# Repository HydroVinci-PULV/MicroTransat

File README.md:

# Architecture
Ceci est une ébauche de l'architecture finale des systèmes embarqués du bateau.

Cette présentation de l'architecture est amenée à évoluer en fonction des besoins du projet.

> **Note :** Les protocoles de communications entre les différents composants ne sont pas représentatifs de la réalité puisque le choix des composants n'est pas définitif à ce stade.

# Composants

## Ordinateur de bord

<p>Considérant que notre bateau autonomme puisse être apparenté à un drone, nous avons fait le choix d'utiliser un <i>flight controller</i> comme ordinateur de bord. C'est pourquoi nous utilisons au sein de notre architecture de navigation un <i>BeagleBone Blue</i> choisit pour sa compatibilité avec .</p>

Vous trouverez plus d'information sur le *BeagleBone Blue* sur [la page dédiée](../../wiki/BeagleBone-Blue) dans le wiki du projet.

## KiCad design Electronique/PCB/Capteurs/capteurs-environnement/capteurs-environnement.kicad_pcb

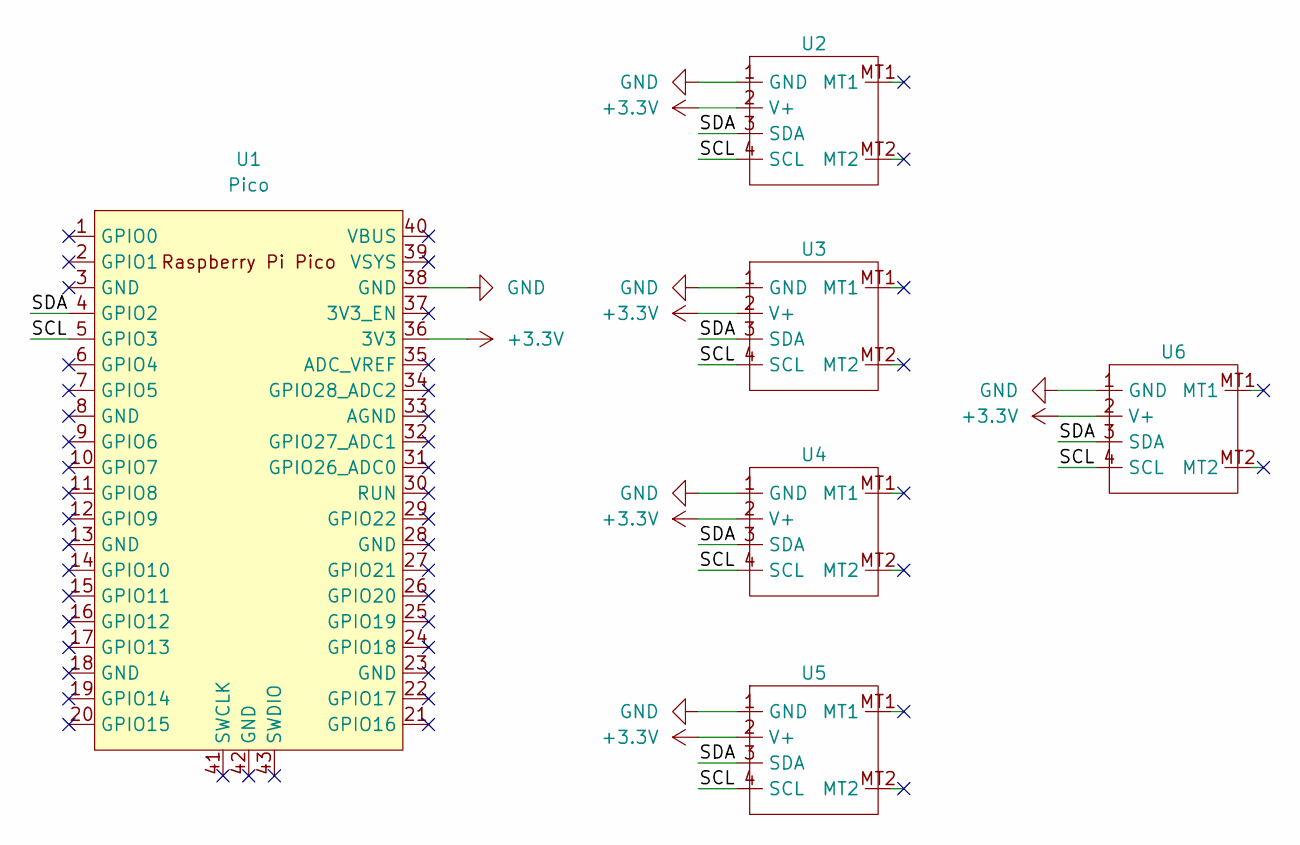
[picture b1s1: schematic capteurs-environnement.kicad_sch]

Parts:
U1: Pico; RPi_Pico_SMD_TH
U2, U3, U4, U5, U6: JST_SH4

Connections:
+3.3V: U1.36 (3V3), U2.2 (V+), U3.2 (V+), U4.2 (V+), U5.2 (V+), U6.2 (V+)
/SCL: U1.5 (GPIO3), U2.4 (SCL), U3.4 (SCL), U4.4 (SCL), U5.4 (SCL), U6.4 (SCL)
/SDA: U1.4 (GPIO2), U2.3 (SDA), U3.3 (SDA), U4.3 (SDA), U5.3 (SDA), U6.3 (SDA)
GND: U1.38 (GND), U2.1 (GND), U3.1 (GND), U4.1 (GND), U5.1 (GND), U6.1 (GND)

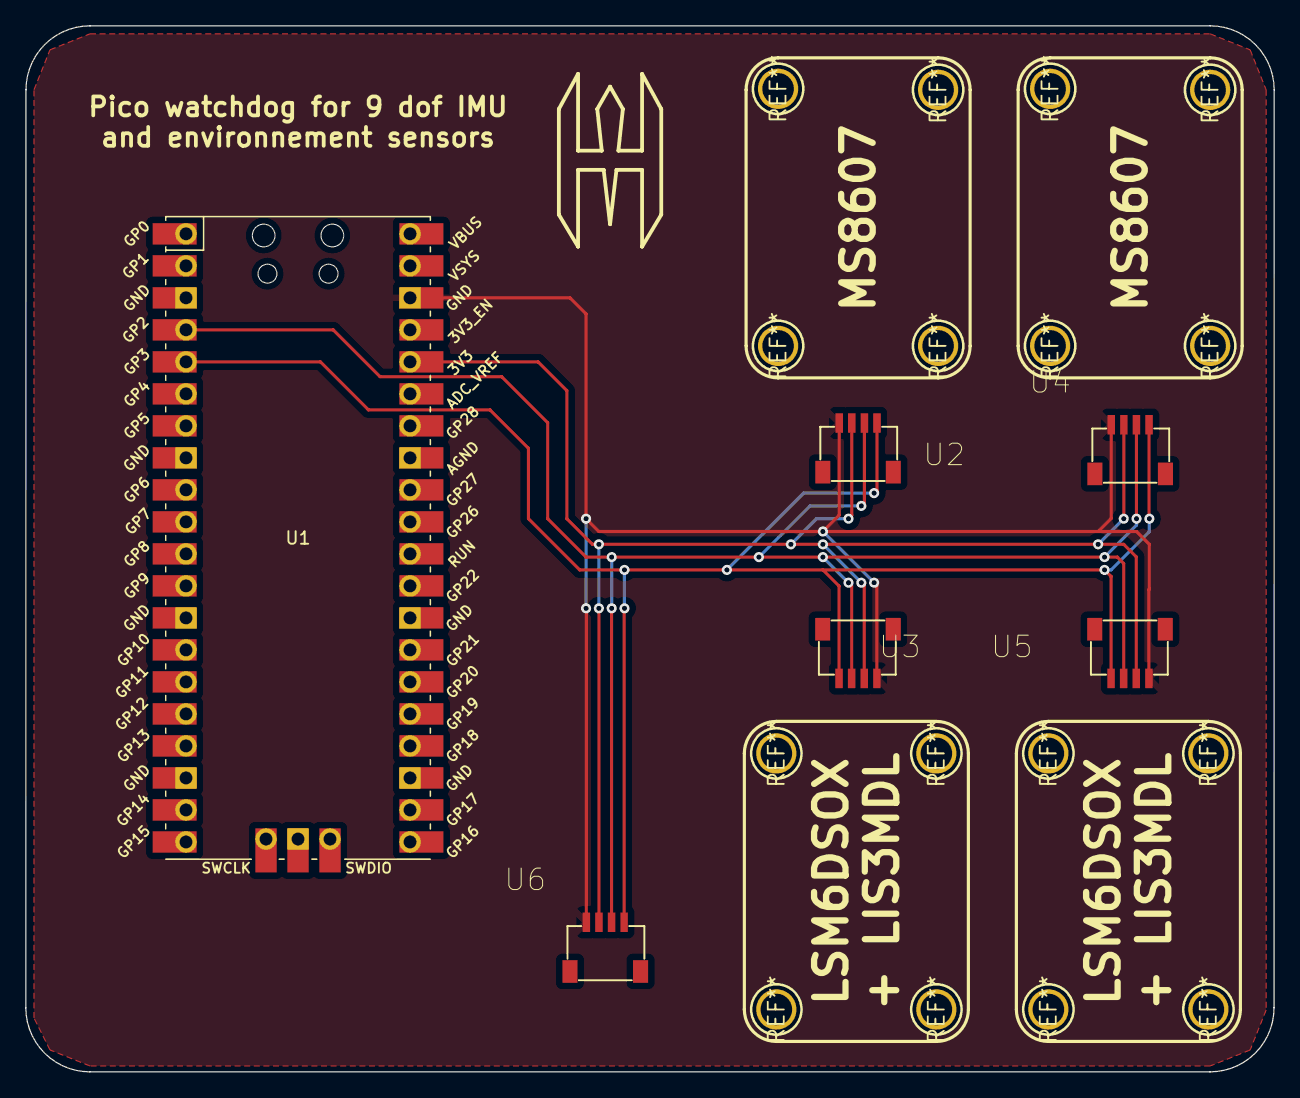
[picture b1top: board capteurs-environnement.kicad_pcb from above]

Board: 2 copper layers, 99.1 x 83.0 mm, 6 parts (0 on the bottom side), 4 nets.

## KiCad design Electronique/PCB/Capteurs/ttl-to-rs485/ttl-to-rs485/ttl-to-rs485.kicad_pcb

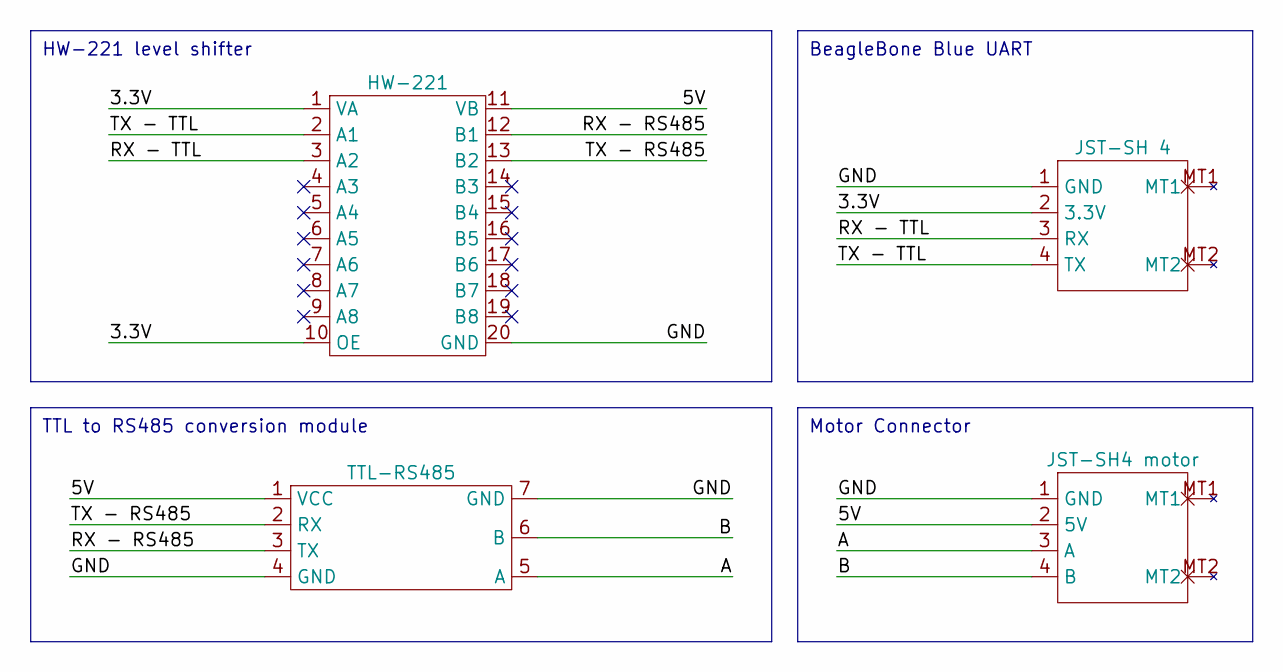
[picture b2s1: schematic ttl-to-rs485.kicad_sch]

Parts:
U1: HW-221
U2: JST-SH 4; JST_SH4
U3: JST-SH4 motor; JST_SH4
U4: TTL-RS485

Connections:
/3.3V: U1.1 (VA), U1.10 (OE), U2.2 (3.3V)
/5V: U1.11 (VB), U3.2 (5V), U4.1 (VCC)
/A: U3.3 (A), U4.5 (A)
/B: U3.4 (B), U4.6 (B)
/GND: U1.20 (GND), U2.1 (GND), U3.1 (GND), U4.4 (GND), U4.7 (GND)
/RX - RS485: U1.12 (B1), U4.3 (TX)
/RX - TTL: U1.3 (A2), U2.3 (RX)
/TX - RS485: U1.13 (B2), U4.2 (RX)
/TX - TTL: U1.2 (A1), U2.4 (TX)

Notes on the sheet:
BeagleBone Blue UART
HW-221 level shifter
Motor Connector
TTL to RS485 conversion module

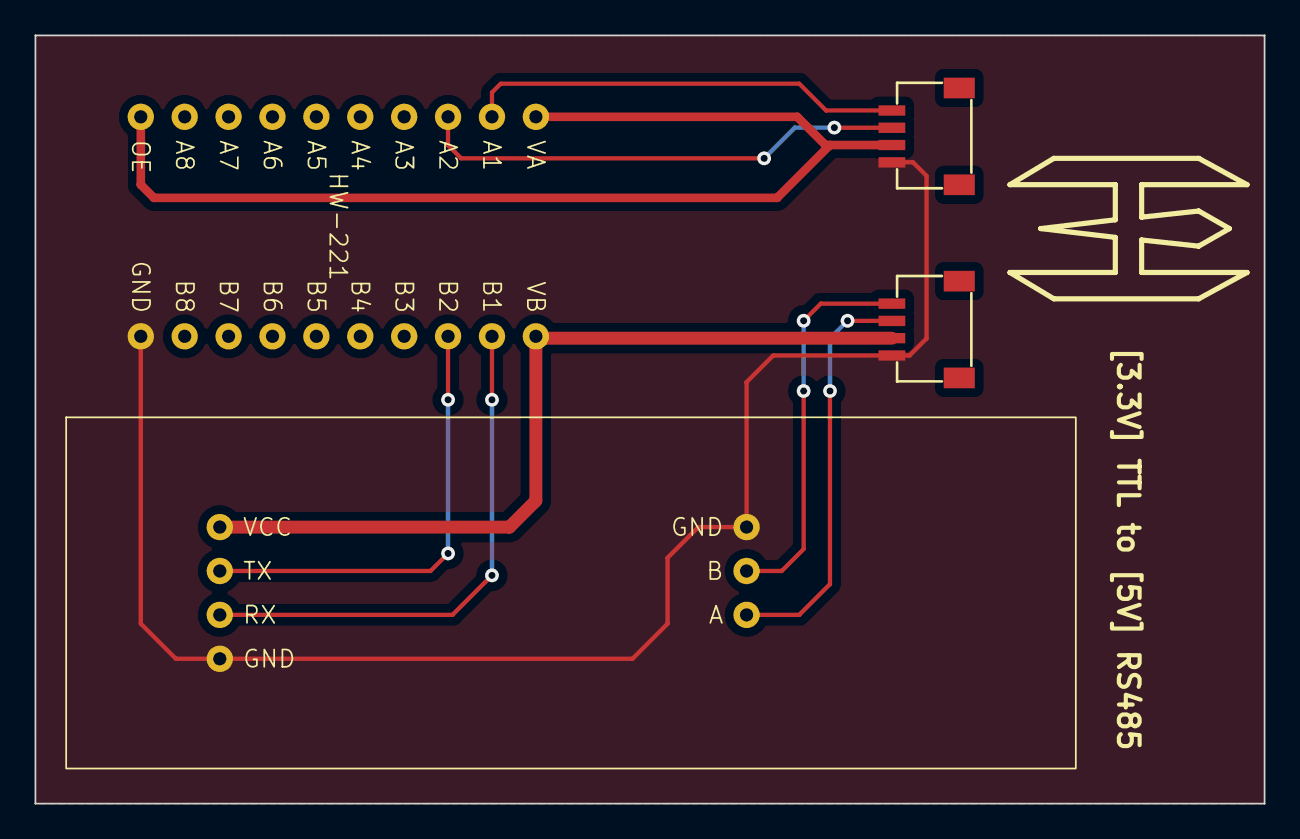
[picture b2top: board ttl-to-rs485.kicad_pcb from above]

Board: 2 copper layers, 71.1 x 44.5 mm, 4 parts (0 on the bottom side), 9 nets.

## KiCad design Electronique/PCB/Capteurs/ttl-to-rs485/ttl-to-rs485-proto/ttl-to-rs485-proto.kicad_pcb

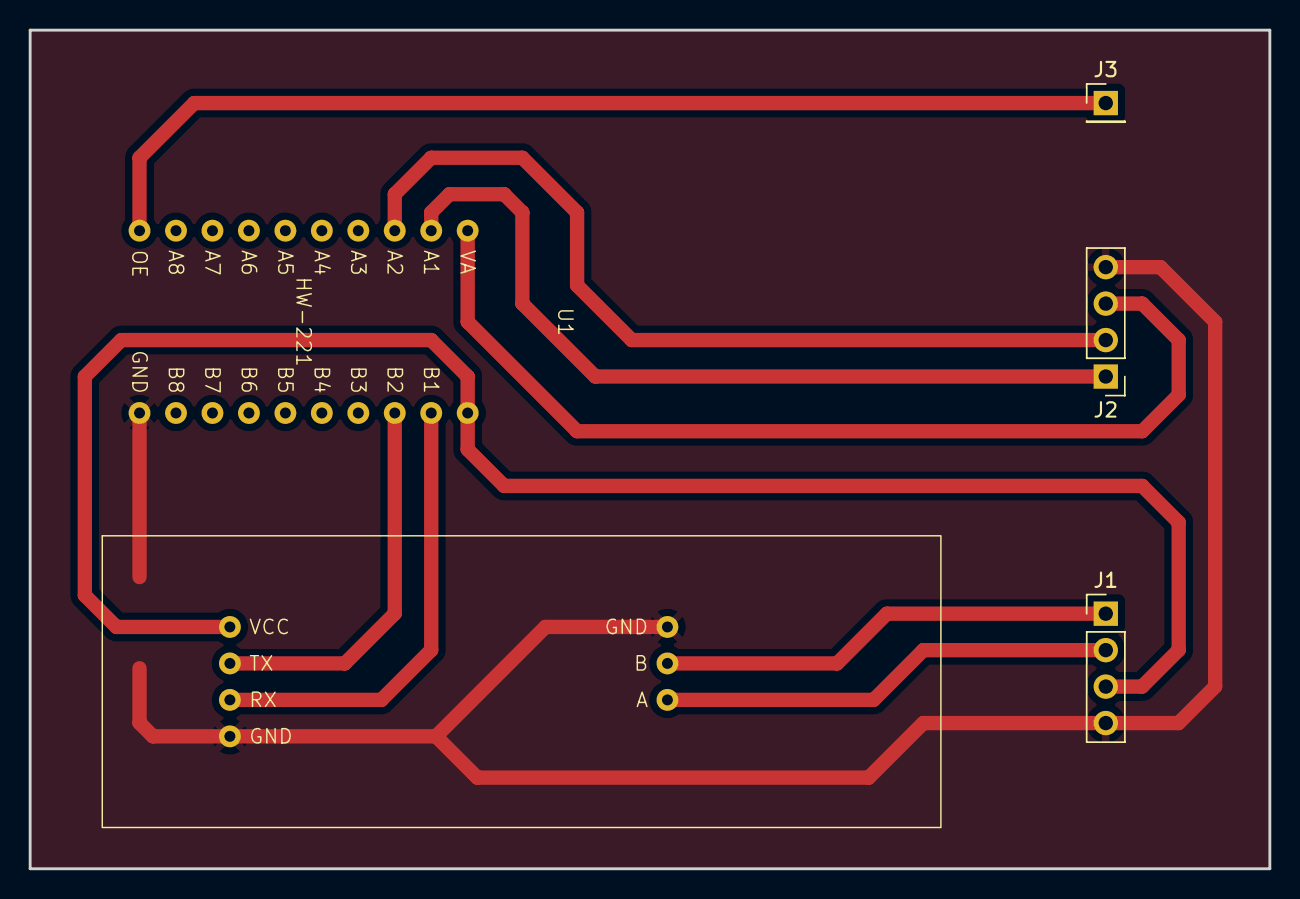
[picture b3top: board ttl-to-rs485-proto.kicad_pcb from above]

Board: 2 copper layers, 86.4 x 58.4 mm, 5 parts (0 on the bottom side), 10 nets.

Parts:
J1, J2: Conn_01x04_Pin; PinHeader_1x04_P2.54mm_Vertical
J3: Conn_01x01_Pin; PinHeader_1x01_P2.54mm_Vertical
U1: HW-221
U2: TTL-RS485

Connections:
/3.3V: J2.3, U1.1 (VA)
/5V: J1.3, U1.11 (VB), U2.1 (VCC)
/A: J1.2, U2.5 (A)
/B: J1.1, U2.6 (B)
/GND: J1.4, J2.4, U1.20 (GND), U2.4 (GND), U2.7 (GND)
/OUT_ENABLE: J3.1, U1.10 (OE)
/RX - RS485: U1.12 (B1), U2.3 (TX)
/RX - TTL: J2.2, U1.3 (A2)
/TX - RS485: U1.13 (B2), U2.2 (RX)
/TX - TTL: J2.1, U1.2 (A1)

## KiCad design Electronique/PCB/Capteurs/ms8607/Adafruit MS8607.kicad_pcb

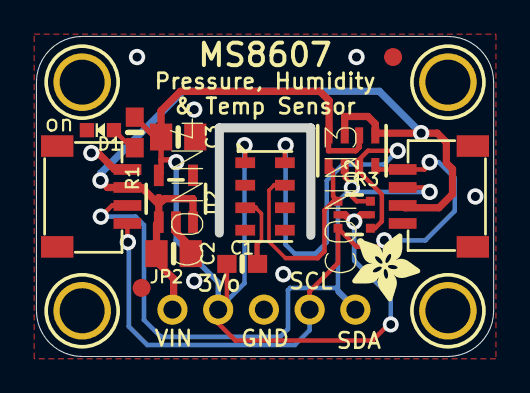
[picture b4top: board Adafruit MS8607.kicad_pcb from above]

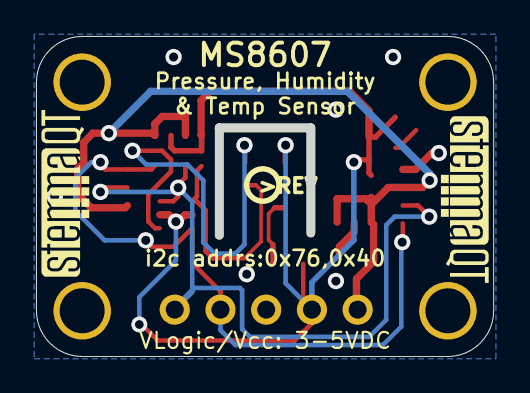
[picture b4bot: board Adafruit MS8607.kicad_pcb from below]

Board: 2 copper layers, 25.4 x 17.8 mm, 22 parts (3 on the bottom side), 8 nets.

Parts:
C1: 0.1uF; 0603-NO
C2, C3: 10uF; 0805-NO
CONN3, CONN4: STEMMA_I2C_QT; JST_SH4
D1: GREEN; CHIPLED_0603_NOOUTLINE
FID3, FID4: FIDUCIAL_1MM
JP2: 1X05_ROUND
Q2: BSS138; SOT363
R1: 10K; 0603-NO
R3: 10K; RESPACK_4X0603
U2: AP2112K-3.3; SOT23-5
U$1, U$17, U$19, U$21: MOUNTINGHOLE2.5; MOUNTINGHOLE_2.5_PLATED
U$22: ADAFRUIT_3.5MM
U$25: PCBFEAT-REV-040
U$30, U$31: STEMMAQT
X1: MS8607

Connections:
3.3V: C1.1, C3.1, JP2.2, Q2.2, Q2.5, R1.1, R3.2, R3.4, U2.5, X1.1
GND: C1.2, C2.2, C3.2, CONN3.1, CONN3.MT1, CONN3.MT2, CONN4.1, CONN4.MT1, CONN4.MT2, D1.C, JP2.3, U2.2, X1.3
unnamed: D1.A, R1.2
SCL: CONN3.4, CONN4.4, JP2.4, Q2.6, R3.8
SCL_3V: Q2.1, R3.7, X1.8
SDA: CONN3.3, CONN4.3, JP2.5, Q2.3, R3.6
SDA_3V: Q2.4, R3.5, X1.7
VCC: C2.1, CONN3.2, CONN4.2, JP2.1, R3.1, R3.3, U2.1, U2.3

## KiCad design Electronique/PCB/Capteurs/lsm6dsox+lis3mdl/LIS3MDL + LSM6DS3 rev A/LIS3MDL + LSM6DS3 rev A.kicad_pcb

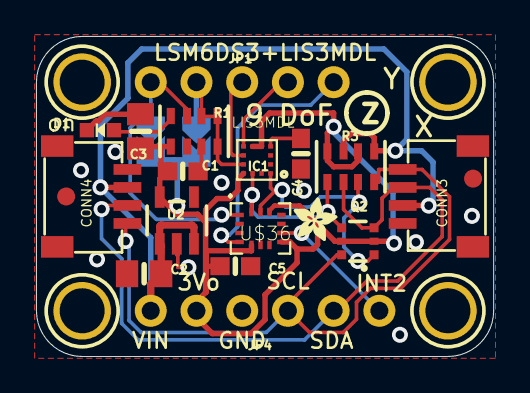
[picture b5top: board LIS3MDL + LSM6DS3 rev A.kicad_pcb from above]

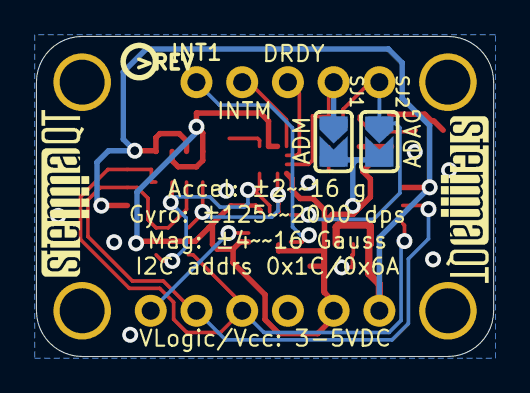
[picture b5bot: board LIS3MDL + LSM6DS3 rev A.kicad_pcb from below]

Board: 2 copper layers, 25.4 x 17.8 mm, 28 parts (5 on the bottom side), 15 nets.

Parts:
C1, C4: 0.1uF; 0603-NO
C2, C3: 10uF; 0805-NO
C5: 1uF; 0603-NO
CONN3, CONN4: STEMMA_I2C_QT; JST_SH4
D1: GREEN; CHIPLED_0603_NOOUTLINE
FID3, FID4: FIDUCIAL_1MM
IC1: LIS3MDL; LGA12_2X2MM
JP1: 1X05_ROUND_70
JP4: 1X06_ROUND_70
Q2: BSS138; SOT363
R1, R3: 10K; RESPACK_4X0603
SJ1, SJ2: SOLDERJUMPER_ARROW_NOPASTE
U2: AP2112K-3.3; SOT23-5
U$1, U$17, U$19, U$21: MOUNTINGHOLE2.5; MOUNTINGHOLE_2.5_PLATED
U$20: ADAFRUIT_2.5MM
U$25: PCBFEAT-REV-040
U$30, U$31: STEMMAQT
U$36: LSM6DS3; LGA-14L

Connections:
3.3V: C1.1, C3.1, C5.1, IC1.5, IC1.6, IC1.10, JP4.2, Q2.2, Q2.5, R1.1, R3.2, R3.4, SJ1.2, SJ2.2, U2.5, U$36.5, U$36.8, U$36.12
ADAG: JP1.1, R1.7, SJ2.1, U$36.1
ADM: IC1.9, JP1.2, R1.4, R1.5, R1.6, SJ1.1
CAP: C4.1, IC1.4
DRDY: IC1.8, JP1.3
GND: C1.2, C2.2, C3.2, C4.2, C5.2, CONN3.1, CONN3.MT1, CONN3.MT2, CONN4.1, CONN4.MT1, CONN4.MT2, D1.C, IC1.2, IC1.3, IC1.12, JP4.3, R1.2, R1.3, U2.2, U$36.6, U$36.7
INT1: JP1.5, U$36.4
INT2: JP4.6, U$36.9
INTM: IC1.7, JP1.4
unnamed: D1.A, R1.8
SCL: CONN3.4, CONN4.4, JP4.4, Q2.6, R3.8
SCL_3V: IC1.1, Q2.1, R3.7, U$36.13
SDA: CONN3.3, CONN4.3, JP4.5, Q2.3, R3.6
SDA_3V: IC1.11, Q2.4, R3.5, U$36.14
VCC: C2.1, CONN3.2, CONN4.2, JP4.1, R3.1, R3.3, U2.1, U2.3

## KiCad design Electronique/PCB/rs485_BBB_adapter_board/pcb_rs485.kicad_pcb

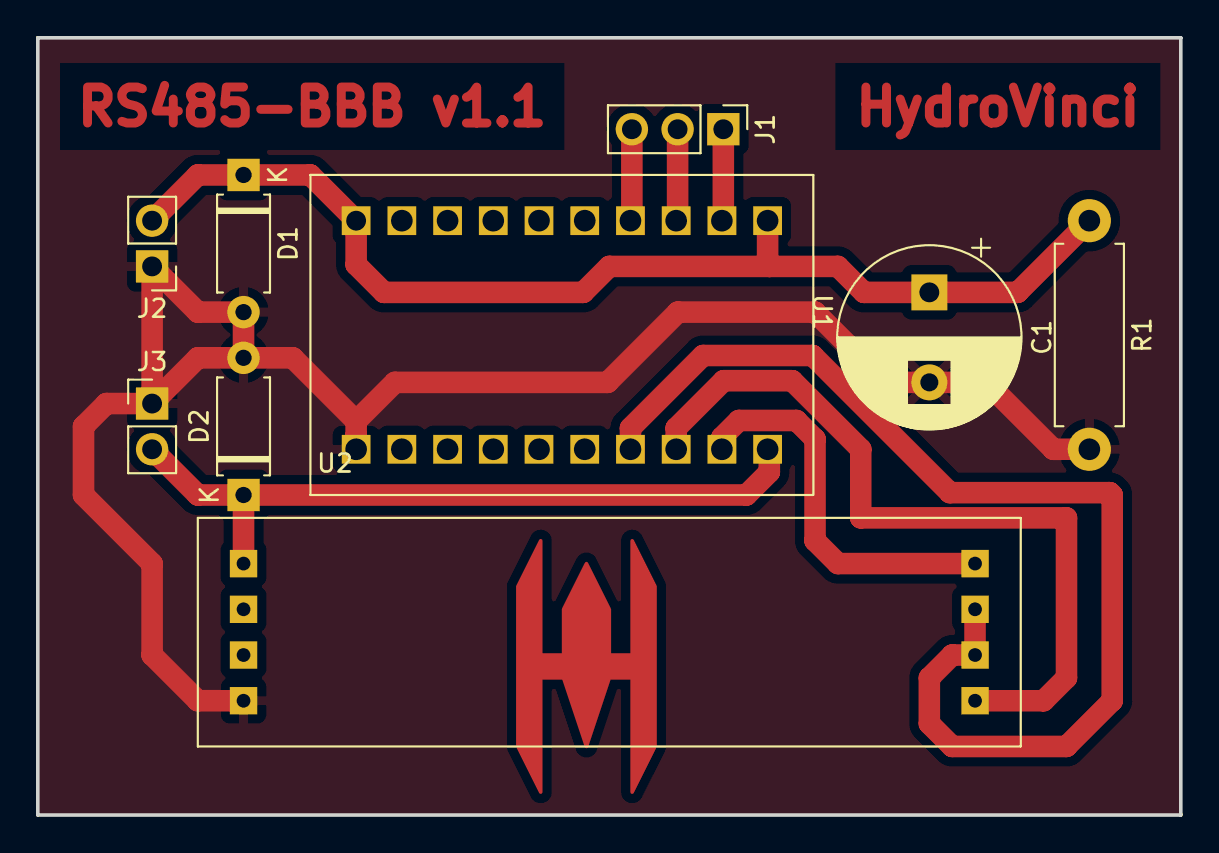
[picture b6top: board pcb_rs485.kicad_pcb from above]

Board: 2 copper layers, 63.5 x 43.2 mm, 9 parts (0 on the bottom side), 9 nets.

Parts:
C1: C; CP_Radial_D10.0mm_P5.00mm
D1, D2: D; D_A-405_P7.62mm_Horizontal
J1: Conn_01x03_Male; PinHeader_1x03_P2.54mm_Vertical
J2, J3: Conn_01x02_Male; PinHeader_1x02_P2.54mm_Vertical
R1: R; R_Axial_DIN0411_L9.9mm_D3.6mm_P12.70mm_Horizontal
U1: D0010
U2: MAX485

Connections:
+3.3V: C1.1, D1.1 (K), J2.2, R1.1, U1.1 (VB), U1.10 (GND)
+5V: D2.1 (K), J3.2, U1.11 (VA), U2.1 (RO)
/ENABLE: U1.14 (A3), U2.6 (B), U2.7 (A)
/RX: U1.13 (A2), U2.8 (GND)
/TX: U1.12 (A1), U2.5 (VCC)
GND: C1.2, D1.2 (A), D2.2 (A), J2.1, J3.1, R1.2, U1.20 (OE), U2.4 (DI)
unnamed: J1.1, U1.2 (B1)
unnamed: J1.2, U1.3 (B2)
unnamed: J1.3, U1.4 (B3)

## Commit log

2021-12-15 navigation algorithms research
2022-01-16 compressor
2022-01-16 Modélisations ordinateur de bord
2022-01-17 Modélisation bateau
2022-01-17 décompressor
2022-01-18 compatibilité solidworks
2022-01-18 autres modé
2022-02-04 decompress : ok pour lat
2022-02-04 data to send
2022-02-05 gps done + unit tests + explications
2022-02-05 debug instructions
2022-02-05 start boat speed compression
2022-02-05 boat speed + data concat
2022-02-05 clean
2022-02-05 updated instruction with unit test
2022-02-05 bits
2022-02-21 logos
2022-02-24 update banner
2022-03-08 Update telemetry.c
    added compression and decompression for heading
2022-04-06 Add architecture v3 to readme
2022-04-06 add paraph on flight controller
2022-04-06 fix wiki page url
2022-04-19 start rust conversion
2022-04-19 Create LICENSE
2022-04-22 j'enleve la v3
2022-04-22 mise a jour archi
2022-05-30 genetic algo for navigation
2022-06-08 bug correction in concat + added unit tests
2022-06-08 bug correction + added unit tests
2022-07-17 draft of rs485 pcb
2022-08-23 BBB pinout
2023-02-01 cad files for adafruit temp/hum/pres sensor + imu
2023-02-02 pcb files for sensors
2023-03-09 update to pcb for environnement sensors + external libs
2023-03-22 kicad schematic for ttl to rs485 conversion module
2023-03-26 ttl to rs485 proto pcb
2023-03-26 update to ttl to rs485 pcb
2023-04-01 pcb updates
2026-04-14 Bump rand from 0.8.5 to 0.9.3 in /Télémetrie
    Bumps [rand](https://github.com/rust-random/rand) from 0.8.5 to 0.9.3.
    - [Release notes](https://github.com/rust-random/rand/releases)
    - [Changelog](https://github.com/rust-random/rand/blob/0.9.3/CHANGELOG.md)
    - [Commits](https://github.com/rust-random/rand/compare/0.8.5...0.9.3)
    ---
    updated-dependencies:
2026-04-22 Bump rand from 0.8.5 to 0.8.6 in /Télémetrie
    Bumps [rand](https://github.com/rust-random/rand) from 0.8.5 to 0.8.6.
    - [Release notes](https://github.com/rust-random/rand/releases)
    - [Changelog](https://github.com/rust-random/rand/blob/0.8.6/CHANGELOG.md)
    - [Commits](https://github.com/rust-random/rand/compare/0.8.5...0.8.6)
    ---
    updated-dependencies:
